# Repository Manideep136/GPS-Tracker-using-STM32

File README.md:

# GPS-Tracker-using-STM32

A custom PCB design for an STM32-based GPS tracking system using the SIM808 GPS/GPRS module.

This project is based on the concept of a GPS tracker using an STM32 microcontroller and SIM808 module. The main focus of this project is the **schematic design, component selection, PCB layout, routing, and design-rule verification using KiCad**.

> ⚠️ **Project Status:** PCB design completed in KiCad.  
> The PCB has **not been manufactured or physically tested yet**.

## 📌 Project Overview

The objective of this project is to design a compact custom PCB capable of integrating the main hardware required for a GPS tracking system.

The PCB is designed around:

- STM32 microcontroller
- SIM808 GPS/GPRS module
- DC-DC power regulation
- GPS and GSM/GPRS antenna interfaces
- SIM card interface
- UART communication
- Programming/debugging interface
- Status indicators
- Supporting capacitors, resistors, and protection components

The complete PCB was designed using **KiCad EDA**.

---

## 🧠 System Architecture

```text
                  ┌──────────────────────┐
                  │      POWER INPUT     │
                  └──────────┬───────────┘
                             │
                             ▼
                  ┌──────────────────────┐
                  │   POWER REGULATION   │
                  │      DC-DC / LDO     │
                  └──────────┬───────────┘
                             │
                             ▼
        ┌────────────────────┴────────────────────┐
        │                                         │
        ▼                                         ▼
┌─────────────────┐                     ┌─────────────────┐
│     STM32 MCU   │◄────── UART ───────►│     SIM808      │
│                 │                     │  GPS + GPRS     │
└────────┬────────┘                     └───────┬─────────┘
         │                                      │
         │                                      ├── GPS Antenna
         │                                      │
         │                                      ├── GSM Antenna
         │                                      │
         │                                      └── SIM Card
         │
         ├── Status LEDs
         │
         ├── Reset / User Button
         │
         └── SWD / Debug Interface

⚡ Power Supply Section

The PCB contains a dedicated power regulation section intended to provide the required voltage rails for the STM32 and SIM808 circuitry.

The design includes:

Input power protection
DC-DC voltage conversion
Decoupling capacitors
Filtering
Power distribution to the main circuit

The power section was designed with the high-current requirements of the SIM808 module in mind.

Note: The power circuit has not been physically validated because this PCB has not yet been manufactured.

📡 SIM808 GPS/GPRS Section

The SIM808 module provides:

GPS positioning
GPRS cellular connectivity
UART communication with the STM32
SIM card interface

🧠 STM32 Microcontroller Section

The STM32 acts as the main controller of the GPS tracker.

The PCB includes supporting circuitry such as:

MCU decoupling capacitors
Crystal oscillator
Reset circuit
User button
Status LEDs
SWD programming/debugging interface
UART connection to SIM808

The STM32 communicates with the SIM808 module through UART.

📶 Antenna Interfaces

The PCB provides dedicated interfaces for:

GPS antenna
GSM/GPRS antenna

These interfaces are routed separately to support the GPS and cellular communication sections.

Special attention was given to the routing of the antenna-related signals during PCB layout.

Note: RF performance has not been experimentally validated because the PCB has not been manufactured.

💾 SIM Card Interface

A SIM card interface is included for cellular network connectivity through the SIM808 module.

The PCB provides the required connections between the SIM card holder and the SIM808 module.

🛠️ PCB Design

The PCB was designed using KiCad.

PCB design process
Circuit Concept
      ↓
Schematic Design
      ↓
Component Selection
      ↓
Footprint Assignment
      ↓
PCB Placement
      ↓
PCB Routing
      ↓
Ground Plane
      ↓
Design Rule Check
      ↓
Gerber Generation

KiCad Design
Schematic

The schematic contains the complete electrical design of the GPS tracker, including:

Power supply
STM32
SIM808
SIM interface
Antenna interfaces
LEDs
Buttons
Crystal oscillator
Debug/programming interface
PCB Layout

The PCB layout includes:

Component placement
Signal routing
Power routing
Ground plane
Through-hole and SMD components
Connector interfaces
Antenna connections
📐 Design Considerations

During PCB design, attention was given to:

Component placement
Signal routing
Power distribution
Grounding
Decoupling
Clearance rules
Track widths
Via placement
Connector accessibility
Antenna routing

Design Rule Check (DRC) was used to identify PCB layout issues before manufacturing.

🚧 Current Limitations

This project currently represents the PCB design stage only.

The PCB has not yet been:

Manufactured
Assembled
Powered
Programmed
Tested with a SIM808 module
Tested with a GPS antenna
Tested on a cellular network

Therefore, the electrical and RF performance of the physical board has not yet been experimentally verified.

🔮 Future Work

Future improvements and validation can include:

Manufacturing the PCB
PCB assembly
STM32 firmware development
SIM808 AT-command integration
GPS position acquisition
GPRS communication
MQTT integration
GPS data logging
Vehicle testing
Power-consumption testing
RF performance testing
Hardware debugging and revision

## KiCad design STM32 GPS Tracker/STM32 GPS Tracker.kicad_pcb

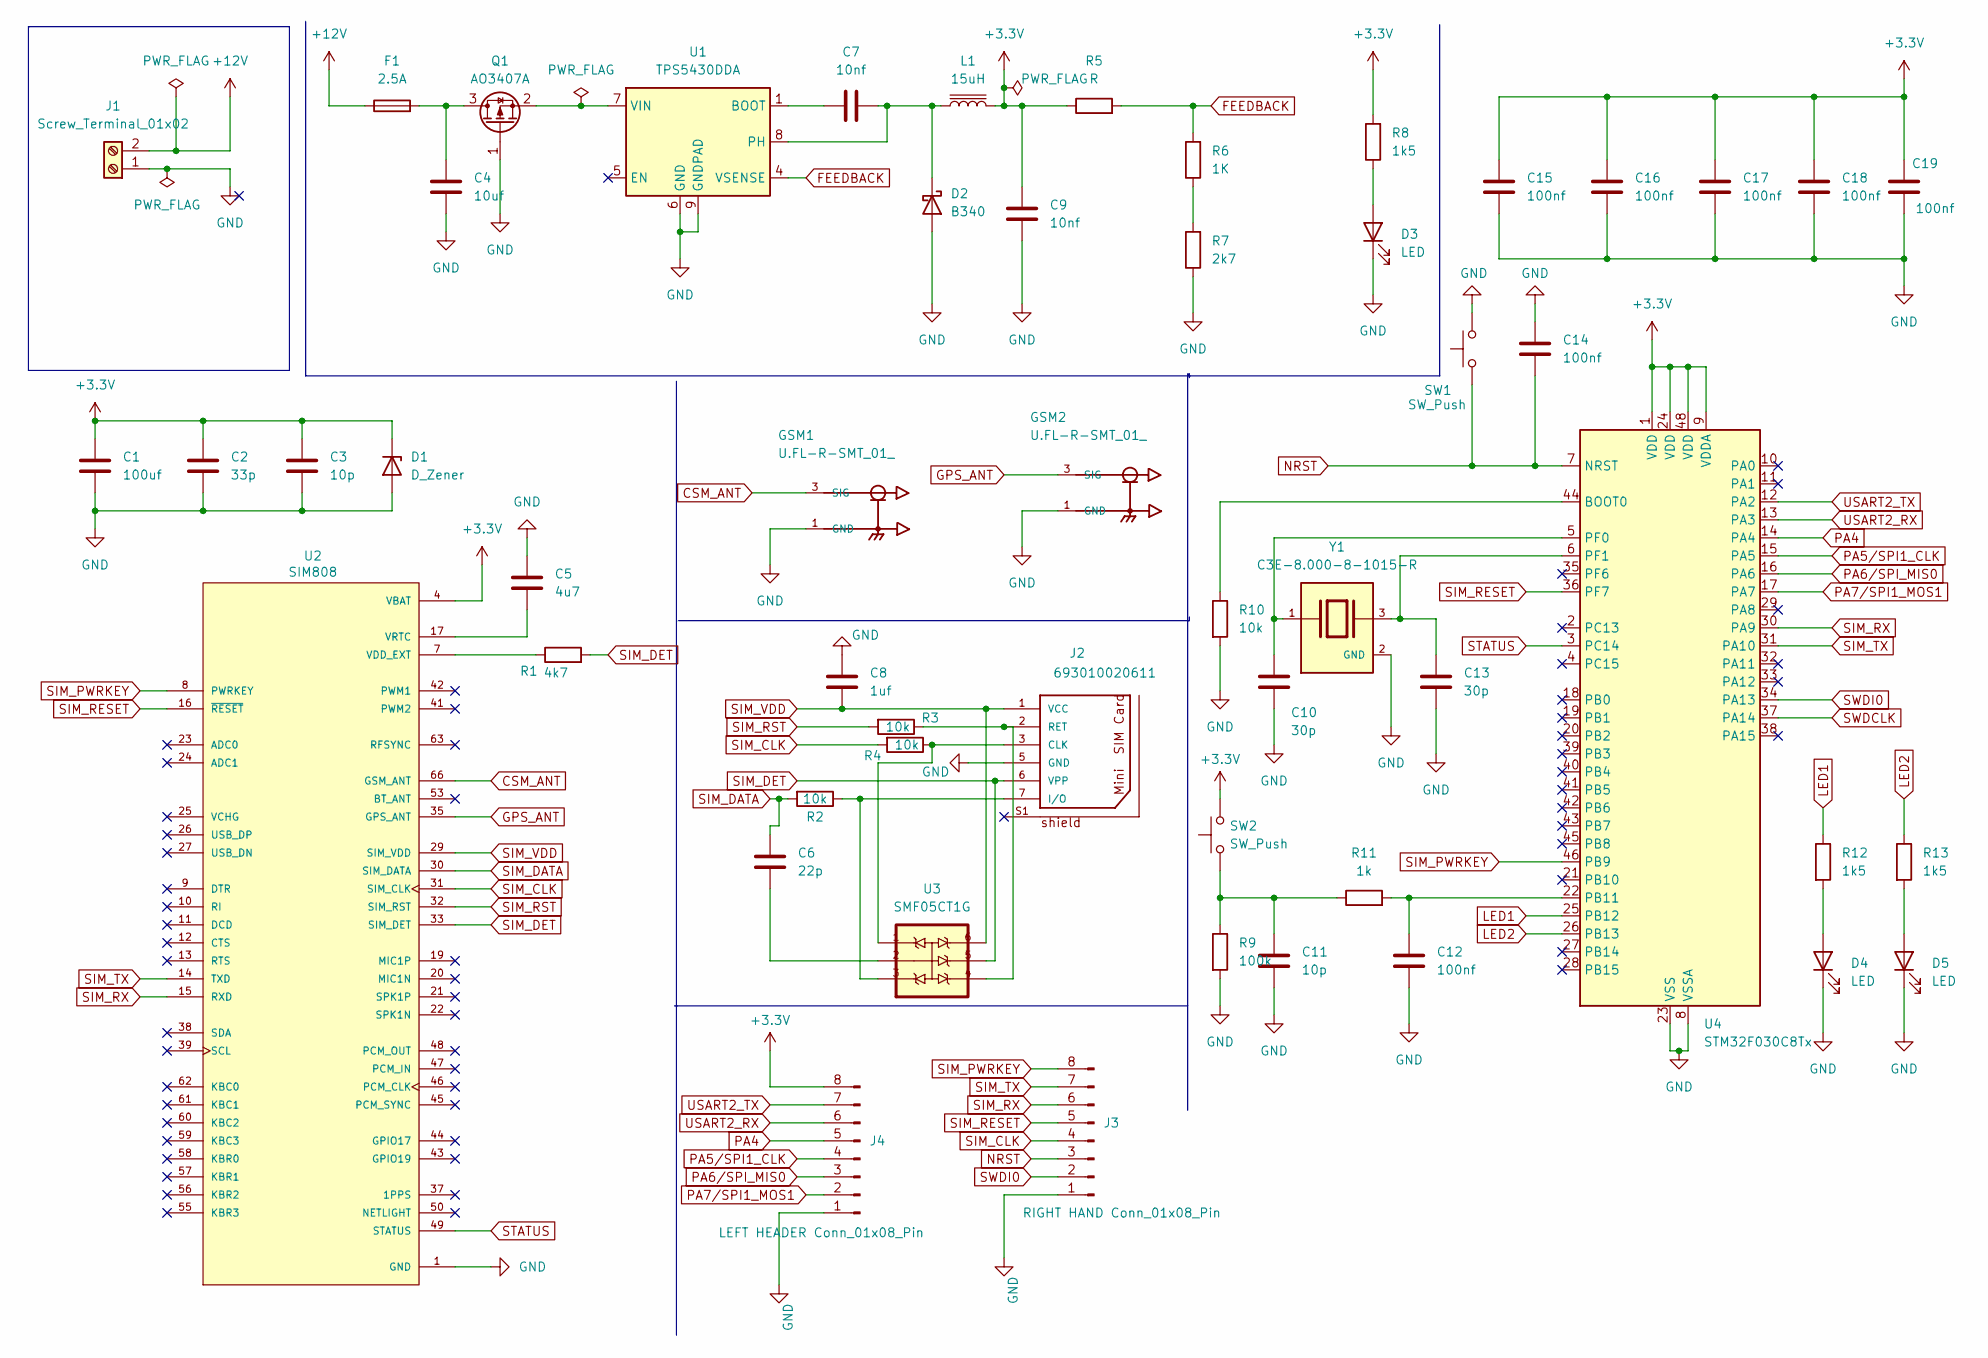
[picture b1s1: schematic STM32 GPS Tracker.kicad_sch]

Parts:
C1: 100uf; C_1206_3216Metric
C2: 33p; C_0402_1005Metric
C3, C11: 10p; C_0402_1005Metric
C4: 10uf; C_0805_2012Metric
C5: 4u7; C_0201_0603Metric
C6: 22p; C_0402_1005Metric
C7: 10nf; C_0201_0603Metric
C8: 1uf; C_0402_1005Metric
C9: 10nf; CP_EIA-7343-15_Kemet-W
C10, C13: 30p; C_0402_1005Metric
C12, C14, C15, C16, C17, C18, C19: 100nf; C_0402_1005Metric
D1: D_Zener; D_0805_2012Metric
D2: B340; D_SMC
D3, D4, D5: LED; LED_0201_0603Metric
F1: 2.5A; Fuse_0402_1005Metric
GSM1, GSM2: U.FL-R-SMT_01_; HRS_U.FL-R-SMT_01_
J1: Screw_Terminal_01x02; Altech_AK100_1x02_P5.00mm
J2: 693010020611
J3: RIGHT HAND Conn_01x08_Pin; TE_826576-8_1x08_P3.96mm_Vertical
J4: LEFT HEADER Conn_01x08_Pin; TE_826576-8_1x08_P3.96mm_Vertical
L1: 15uH; L_10.4x10.4_H4.8
Q1: AO3407A; SOT-23
R1: 4k7; R_0402_1005Metric
R2, R3, R4, R10: 10k; R_0402_1005Metric
R5: R; R_0805_2012Metric
R6: 1K; R_0805_2012Metric
R7: 2k7; R_0805_2012Metric
R8, R12, R13: 1k5; R_0805_2012Metric
R9: 100k; R_0201_0603Metric
R11: 1k; R_0603_1608Metric
SW1, SW2: SW_Push; SW_PUSH_6mm
U1: TPS5430DDA; TI_SO-PowerPAD-8_ThermalVias
U2: SIM808; XCVR_SIM808; PARTREV 1.03
U3: SMF05CT1G; SOT65P210X110-6N
U4: STM32F030C8Tx; LQFP-48_7x7mm_P0.5mm
Y1: C3E-8.000-8-1015-R; XTAL_C3E-8.000-8-1015-R; PARTREV N/A

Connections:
+3.3V: C1.1, C2.1, C3.1, C9.2, C15.2, C16.2, C17.2, C18.2, C19.2, D1.1 (K), J4.8, L1.2, R5.1, R8.2, SW2.2, U2.4 (VBAT), U2.5 (VBAT), U2.6 (VBAT), U4.1 (VDD), U4.9 (VDDA), U4.24 (VDD), U4.48 (VDD)
+12V: F1.1, J1.2
CSM_ANT: GSM1.3 (SIG), U2.66 (GSM_ANT)
FEEDBACK: R5.2, R6.2, U1.4 (VSENSE)
GND: C1.2, C2.2, C3.2, C4.2, C5.1, C8.1, C9.1, C10.1, C11.1, C12.1, C13.1, C14.2, C15.1, C16.1, C17.1, C18.1, C19.1, D1.2 (A), D2.2 (A), D3.1 (K), D4.1 (K), D5.1 (K), GSM1.1 (GND), GSM1.2 (GND), GSM2.1 (GND), GSM2.2 (GND), J1.1, J2.5 (GND), J3.1, J4.1, Q1.1 (G), R7.1, R9.2, R10.2, SW1.2, U1.6 (GND), U1.9 (GNDPAD), U2.1 (GND), U2.2 (GND), U2.3 (GND), U2.18 (GND), U2.28 (GND), U2.34 (GND), U2.36 (GND), U2.40 (GND), U2.51 (GND), U2.52 (GND), U2.54 (GND), U2.64 (GND), U2.65 (GND), U2.67 (GND), U2.68 (GND), U4.8 (VSSA), U4.23 (VSS), U4.47 (VSS), Y1.2 (GND), Y1.4 (GND)
GPS_ANT: GSM2.3 (SIG), U2.35 (GPS_ANT)
LED1: R12.1, U4.25 (PB12)
LED2: R13.1, U4.26 (PB13)
NRST: C14.1, J3.3, SW1.1, U4.7 (NRST)
unnamed: C6.2, U3.2
unnamed: C11.2, R9.1, R11.1, SW2.1
unnamed: C7.2, D2.1 (K), L1.1, U1.8 (PH)
unnamed: D3.2 (A), R8.1
unnamed: D4.2 (A), R12.2
unnamed: D5.2 (A), R13.2
unnamed: J2.3 (CLK), R4.1, U3.1
unnamed: J2.7 (I/O), R2.1, U3.3
unnamed: J2.2 (RET), R3.1, U3.4
unnamed: C4.1, F1.2, Q1.3 (D)
unnamed: Q1.2 (S), U1.7 (VIN)
unnamed: R6.1, R7.2
unnamed: C7.1, U1.1 (BOOT)
unnamed: R1.1, U2.7 (VDD_EXT)
unnamed: C5.2, U2.17 (VRTC)
unnamed: R10.1, U4.44 (BOOT0)
unnamed: C12.2, R11.2, U4.22 (PB11)
unnamed: C10.2, U4.5 (PF0), Y1.1
unnamed: C13.2, U4.6 (PF1), Y1.3
PA4: J4.5, U4.14 (PA4)
PA5/SPI1_CLK: J4.4, U4.15 (PA5)
PA6/SPI_MIS0: J4.3, U4.16 (PA6)
PA7/SPI1_MOS1: J4.2, U4.17 (PA7)
SIM_CLK: J3.4, R4.2, U2.31 (SIM_CLK)
SIM_DATA: C6.1, R2.2, U2.30 (SIM_DATA)
SIM_DET: J2.6 (VPP), R1.2, U2.33 (SIM_DET), U3.5
SIM_PWRKEY: J3.8, U2.8 (PWRKEY), U4.46 (PB9)
SIM_RESET: J3.5, U2.16 (~RESET), U4.36 (PF7)
SIM_RST: R3.2, U2.32 (SIM_RST)
SIM_RX: J3.6, U2.15 (RXD), U4.30 (PA9)
SIM_TX: J3.7, U2.14 (TXD), U4.31 (PA10)
SIM_VDD: C8.2, J2.1 (VCC), U2.29 (SIM_VDD), U3.6
STATUS: U2.49 (STATUS), U4.3 (PC14)
SWDCLK: U4.37 (PA14)
SWDI0: J3.2, U4.34 (PA13)
USART2_RX: J4.6, U4.13 (PA3)
USART2_TX: J4.7, U4.12 (PA2)

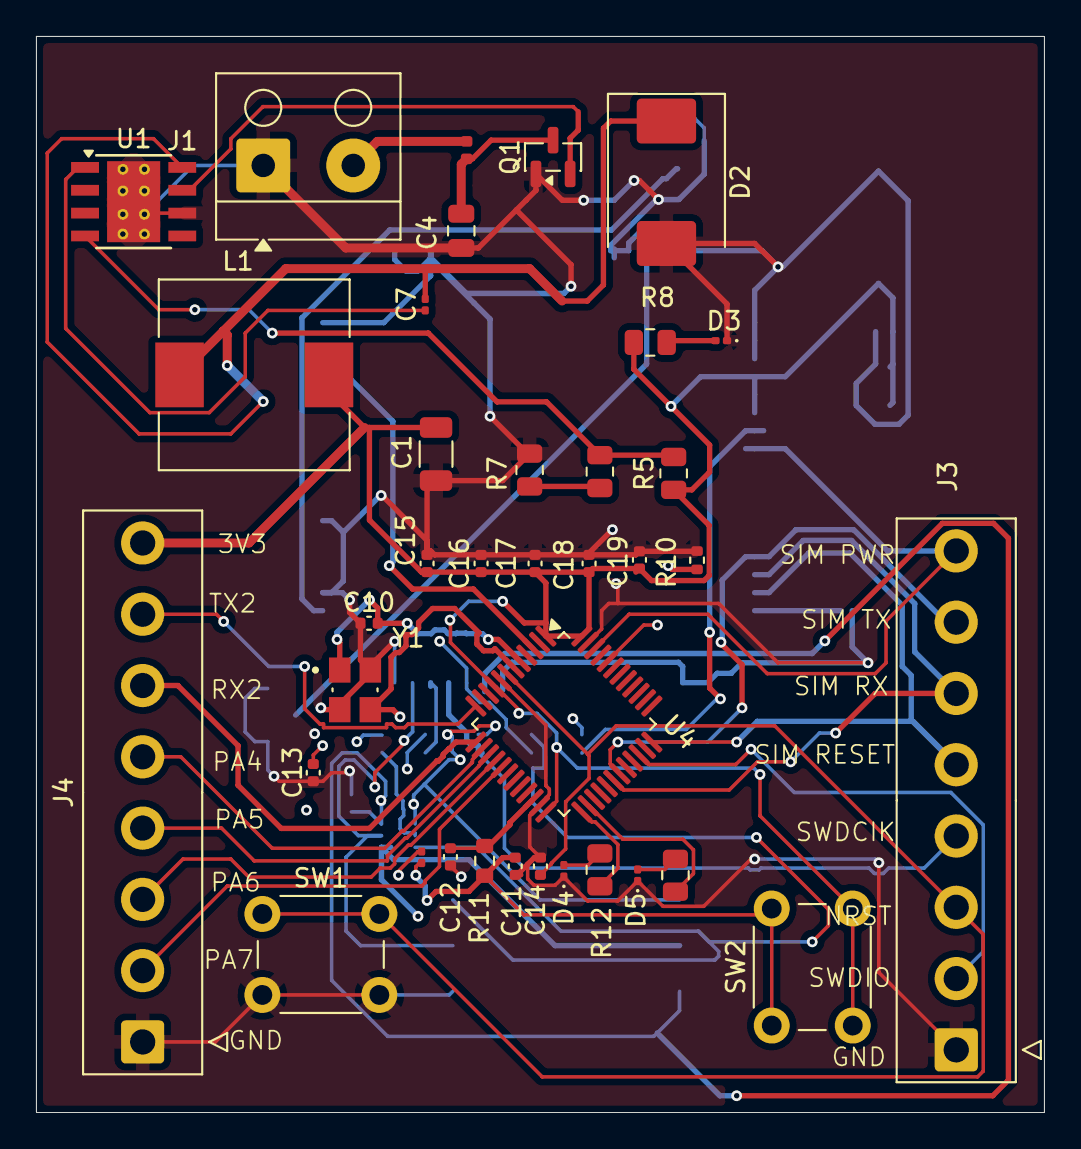
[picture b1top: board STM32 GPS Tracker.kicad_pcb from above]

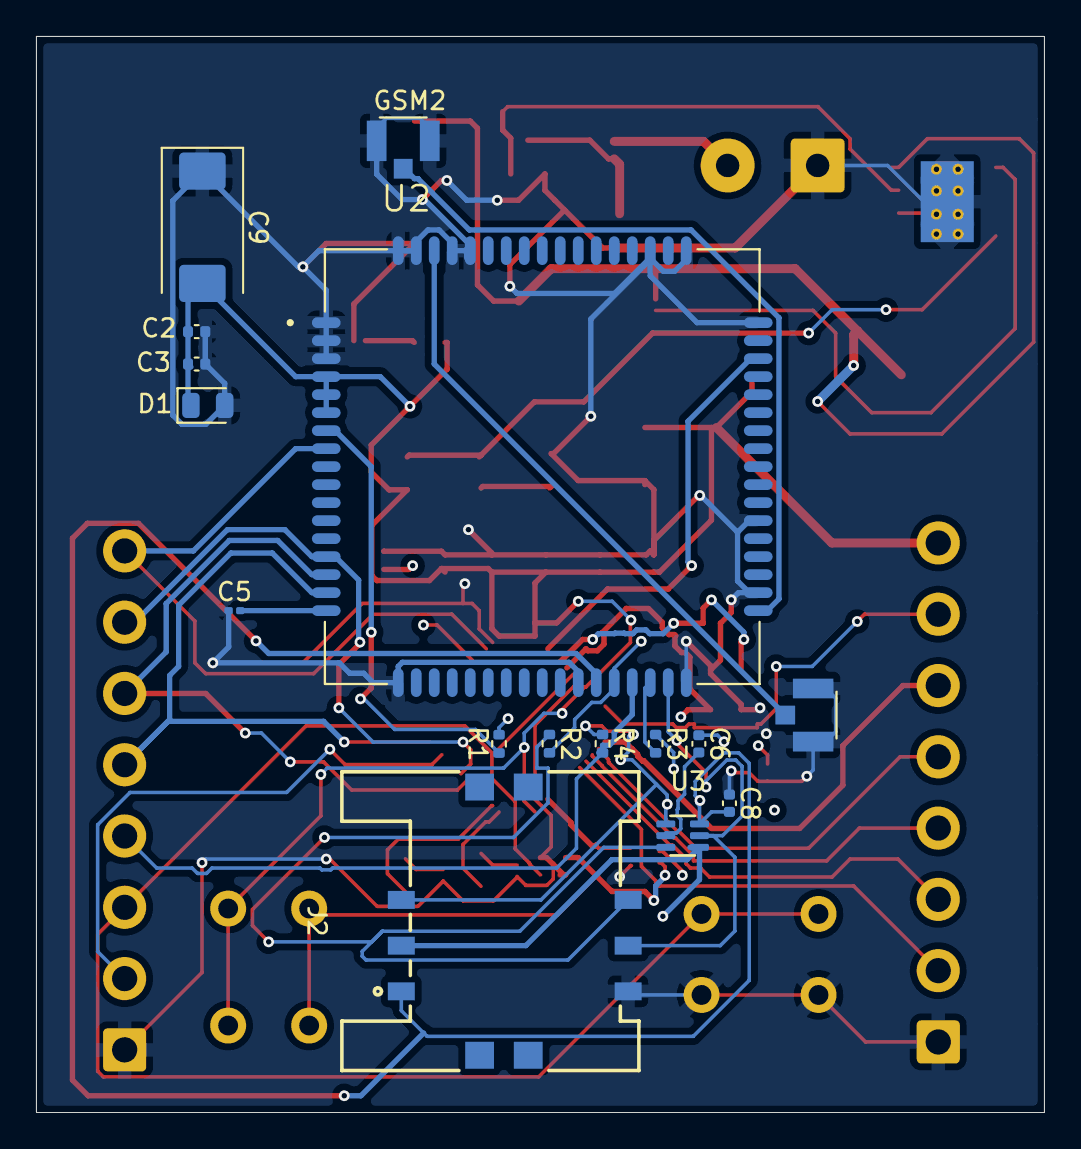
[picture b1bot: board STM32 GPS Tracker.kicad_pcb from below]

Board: 4 copper layers, 56.0 x 59.8 mm, 53 parts (16 on the bottom side), 45 nets.
